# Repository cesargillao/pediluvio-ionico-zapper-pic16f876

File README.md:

# Pediluvio Iónico con Zapper (PIC16F876)

## Se proporciona:
* Diagrama esquemático para emular el funcionamiento (Proteus)
* Diagrama esquemático en PDF
* Diagrama esquemático y PCB (CadSoft Eagle)
* Software en C y ASM con su respectivo HEX (CCS Compiler)

### Si te gusta el proyecto, recomiendo dejar una estrella en el mismo o en mi perfil.
### Eso me inspira a seguir colaborando a la comunidad ❤.

# ⚠ Advertencia ⚠ 
### Este producto no ha sido probado más allá de una emulación mediante software y fue desarrollado con fines educativos. Por lo tanto, el uso que se le quiera dar a este proyecto es responsabilidad de quien lo implemente.

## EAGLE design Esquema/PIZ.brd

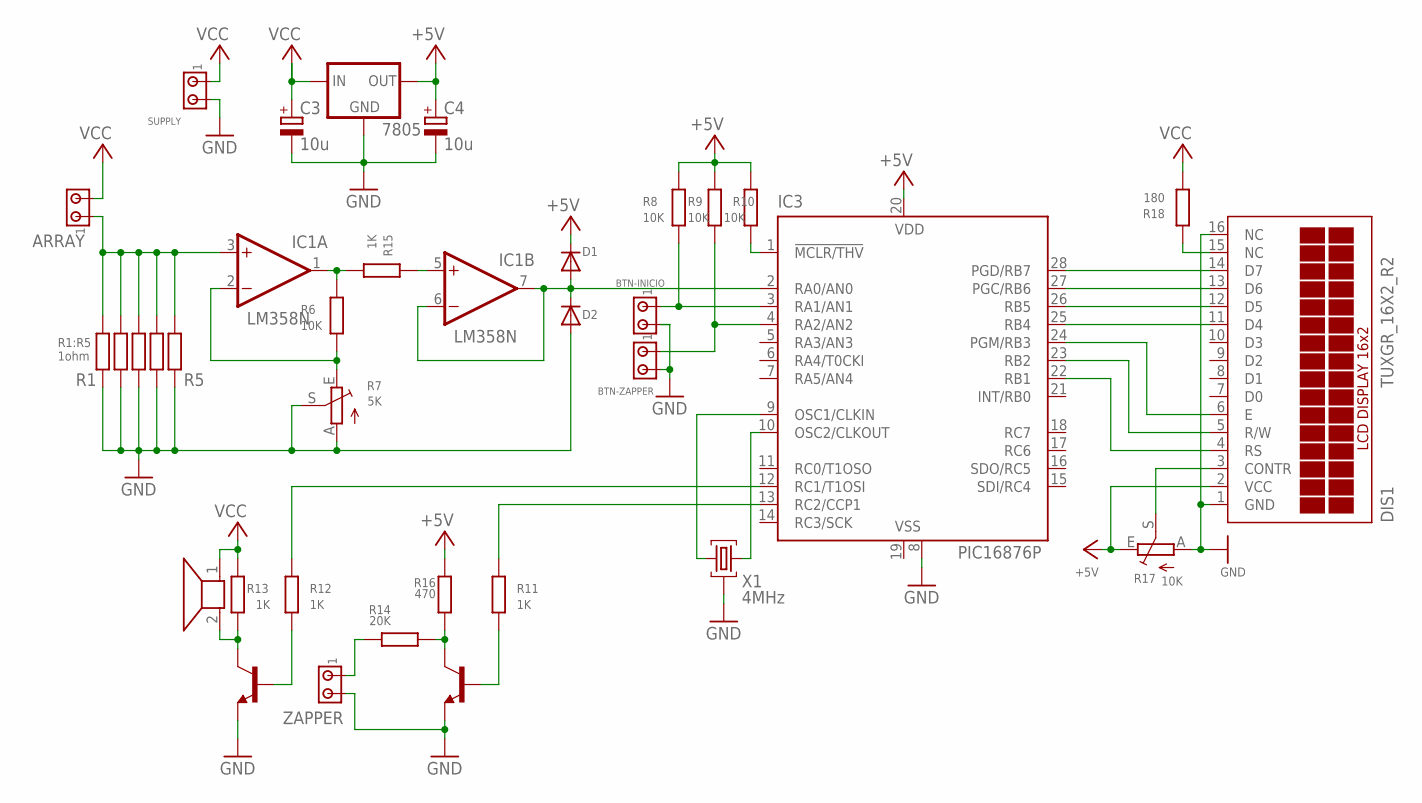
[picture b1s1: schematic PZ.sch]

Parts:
7805: 78XXL
ARRAY: MTA02-156; 1X2MTA
BTN-INICIO: MTA02-100; 10X02MTA
BTN-ZAPPER: MTA02-100; 10X02MTA
C3, C4: 10u; E1,8-4
D1, D2: 1N4148; DO35-7
DIS1: TUXGR_16X2_R2
IC1: LM358N; DIL08
IC3: PIC16876P; DIL28-3
Q2, Q3: 2N3904; TO92
R1, R2, R3, R4, R5: 1; 0204/7
R6, R8, R9, R10: 10K; 0204/7
R7: 5K; B25P
R11, R12, R13, R15: 1K; 0204/7
R14: 20K; 0204/7
R16: 470; 0204/7
R17: 10K; B25P
R18: 180; 0204/7
SP1: AL60P
SUPPLY: MTA02-100; 10X02MTA
X1: 4MHz; HC49U
ZAPPER: MTA02-156; 1X2MTA

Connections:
+5V: 7805.OUT, C4.+, D1.C, DIS1.2 (VCC), IC3.20 (VDD), R8.1, R9.1, R10.1, R16.2, R17.E
GND: 7805.GND, BTN-INICIO.2, BTN-ZAPPER.2, C3.-, C4.-, D2.A, DIS1.1 (GND), DIS1.16 (NC), IC3.8 (VSS), Q2.3 (E), Q3.3 (E), R1.2, R2.2, R3.2, R4.2, R5.2, R7.A, R7.S, R17.A, SUPPLY.2, X1.2, ZAPPER.2
unnamed: ARRAY.1, IC1.3 (+IN), R1.1, R2.1, R3.1, R4.1, R5.1
unnamed: D1.A, D2.C, IC1.6 (-IN), IC1.7 (OUT), IC3.2 (RA0/AN0)
unnamed: IC1.2 (-IN), R6.2, R7.E
unnamed: IC3.1 (!MCLR/THV), R10.2
unnamed: IC3.10 (OSC2/CLKOUT), X1.3
unnamed: BTN-INICIO.1, IC3.3 (RA1/AN1), R8.2
unnamed: IC3.12 (RC1/T1OSI), R12.1
unnamed: BTN-ZAPPER.1, IC3.4 (RA2/AN2), R9.2
unnamed: Q2.2 (B), R11.2
unnamed: Q3.2 (B), R12.2
unnamed: Q3.1 (C), R13.2, SP1.2
unnamed: R14.1, ZAPPER.1
unnamed: Q2.1 (C), R14.2, R16.1
unnamed: DIS1.14 (D7), IC3.28 (PGD/RB7)
unnamed: DIS1.13 (D6), IC3.27 (PGC/RB6)
unnamed: DIS1.12 (D5), IC3.26 (RB5)
unnamed: DIS1.11 (D4), IC3.25 (RB4)
unnamed: DIS1.6 (E), IC3.24 (PGM/RB3)
unnamed: DIS1.5 (R/W), IC3.23 (RB2)
unnamed: DIS1.4 (RS), IC3.22 (RB1)
unnamed: DIS1.15 (NC), R18.1
unnamed: DIS1.3 (CONTR), R17.S
unnamed: IC3.13 (RC2/CCP1), R11.1
unnamed: IC3.9 (OSC1/CLKIN), X1.1
V+: IC1.8 (V+)
V-: IC1.4 (V-)
VCC: 7805.IN, ARRAY.2, C3.+, R13.1, R18.2, SP1.1, SUPPLY.1
VSS: IC3.19 (VSS)

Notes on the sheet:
R1:R5 1ohm

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
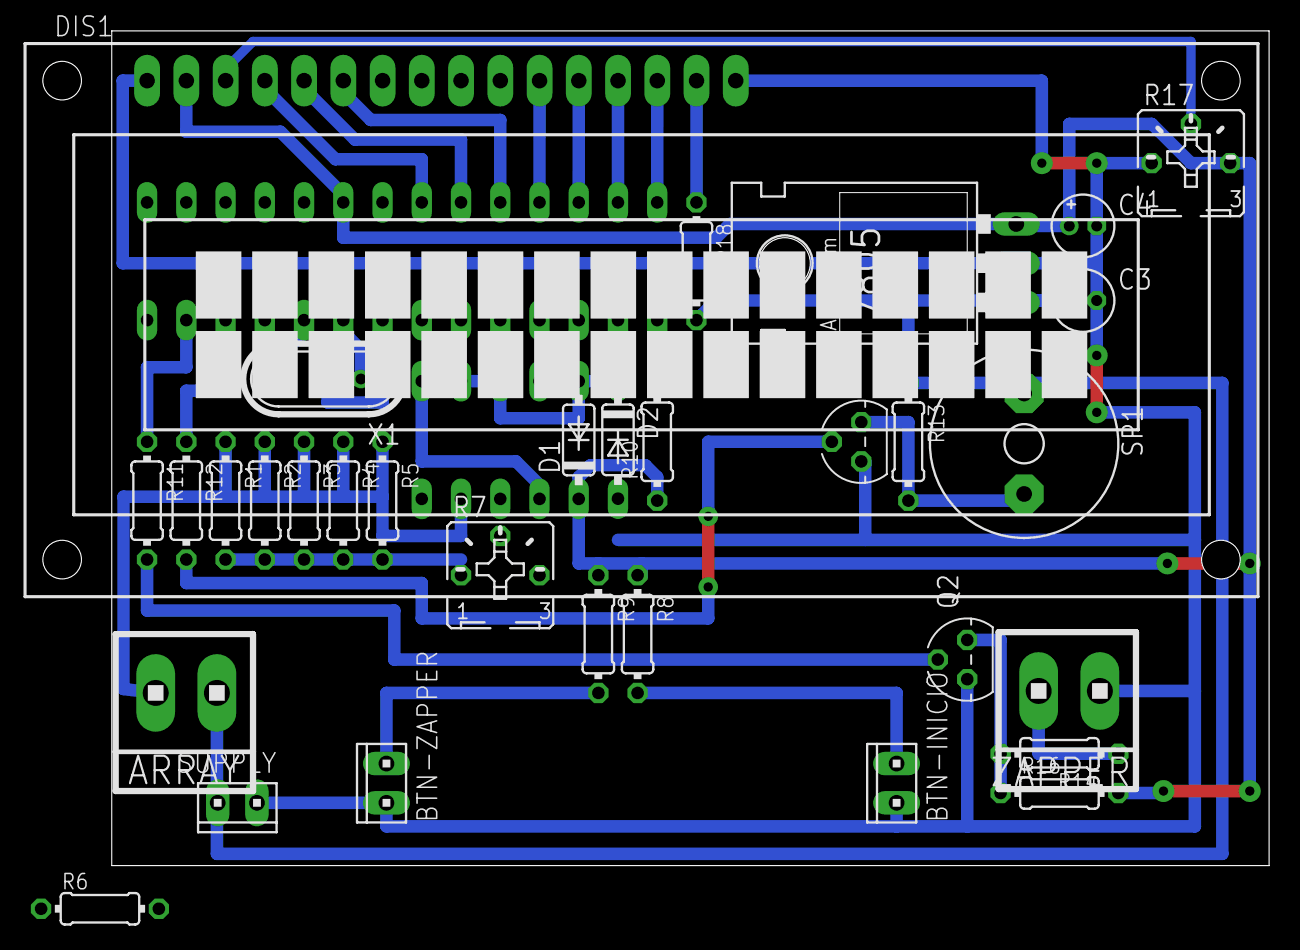
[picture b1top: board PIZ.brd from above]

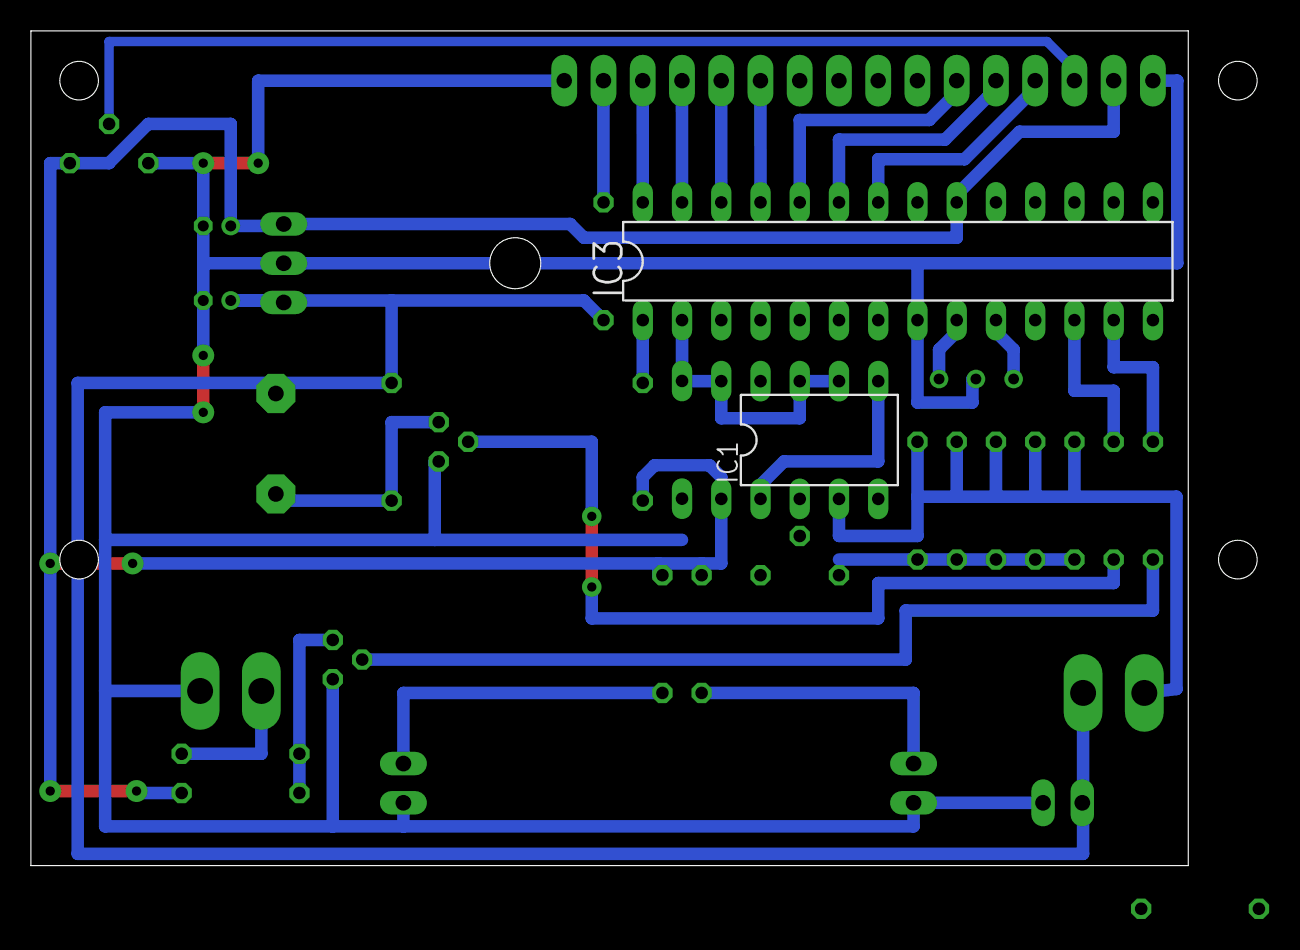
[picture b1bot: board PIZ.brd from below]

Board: 2 copper layers, 74.9 x 54.0 mm, 34 parts (2 on the bottom side), 28 nets.
